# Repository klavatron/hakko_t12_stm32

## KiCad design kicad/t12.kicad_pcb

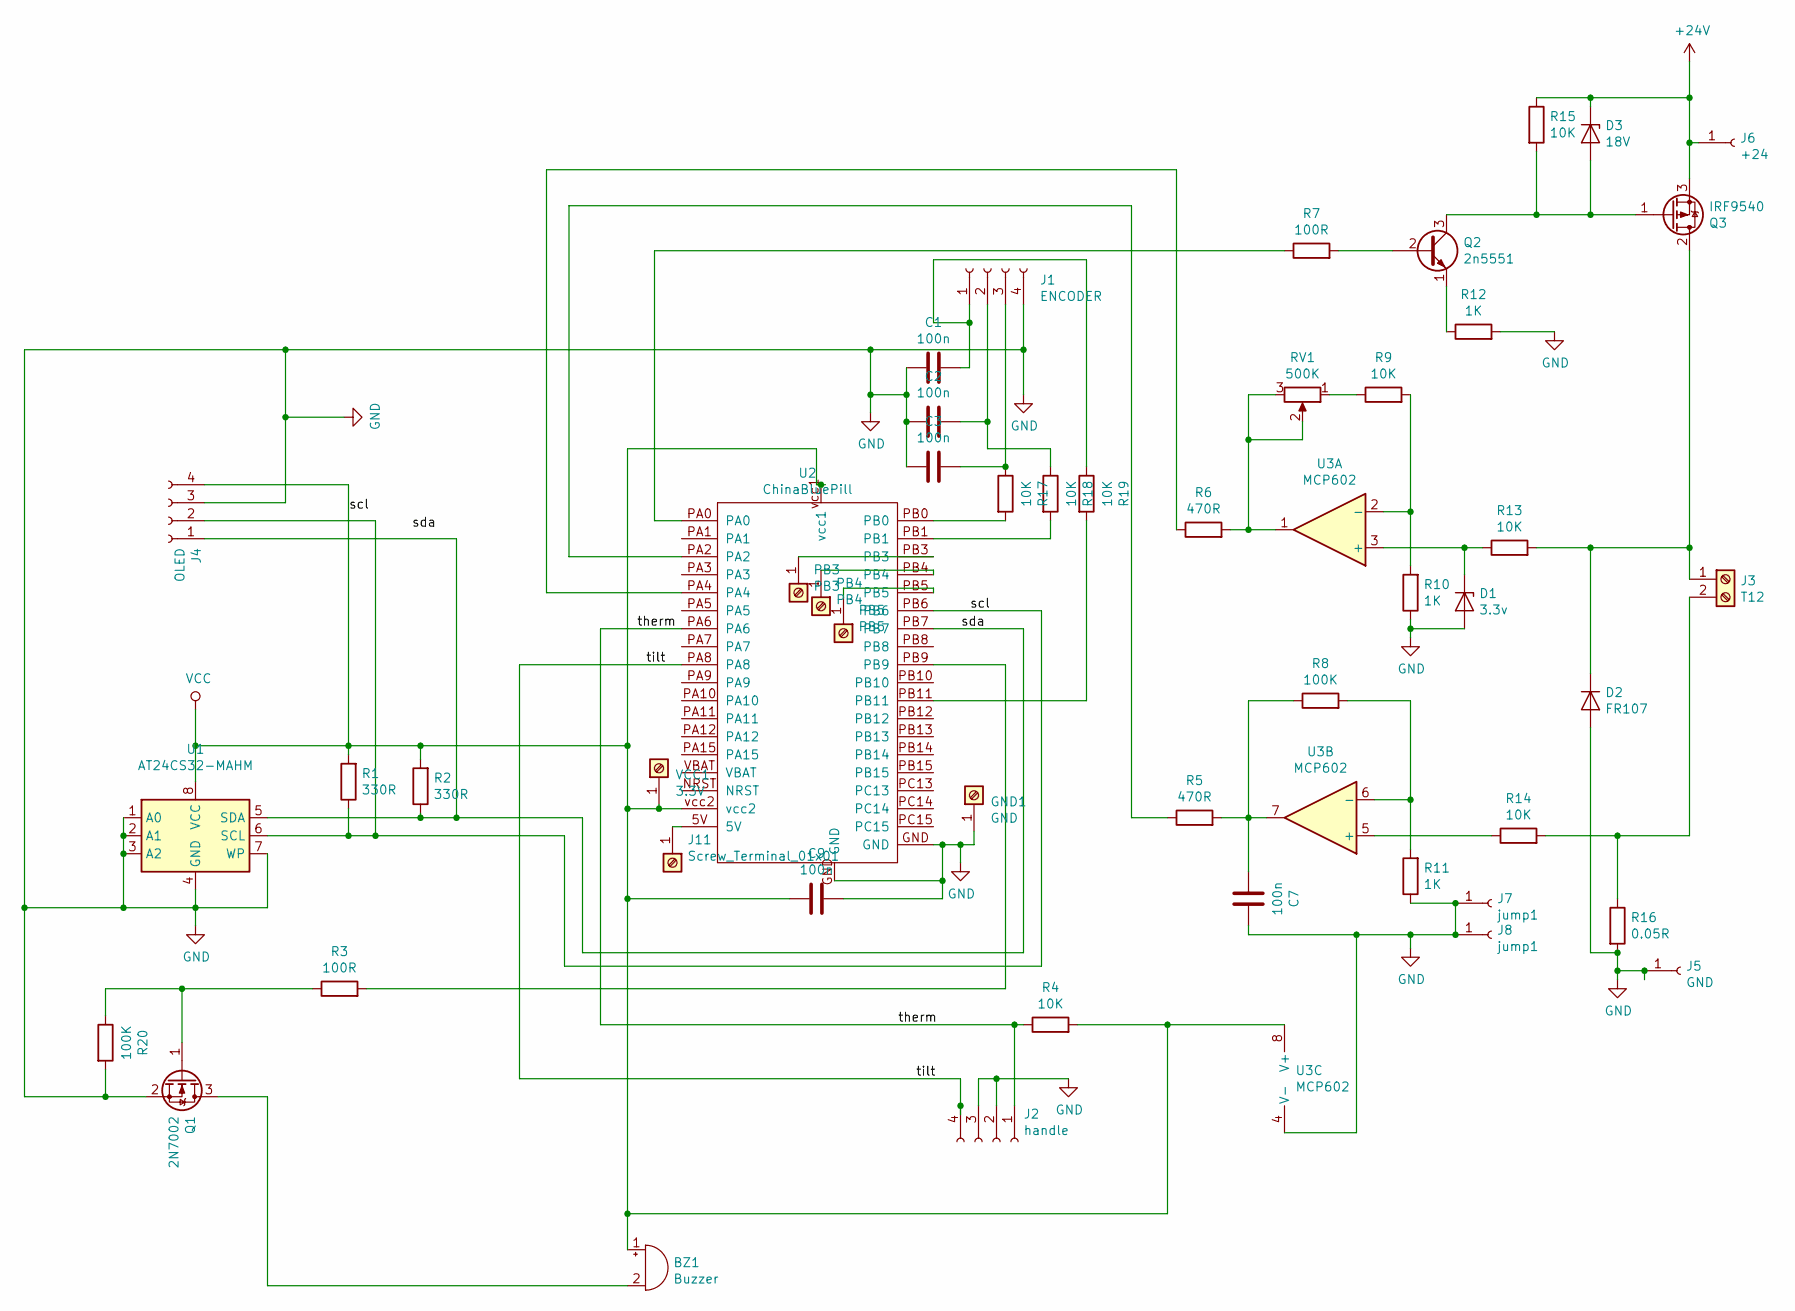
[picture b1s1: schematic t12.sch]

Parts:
BZ1: Buzzer; PinHeader_1x02_P2.54mm_Vertical
C1, C2, C3, C7, C9: 100n; C_1806_4516Metric
D1: 3.3v; D_DO-41_SOD81_P10.16mm_Horizontal
D2: FR107; D_DO-41_SOD81_P12.70mm_Horizontal
D3: 18V; D_DO-41_SOD81_P10.16mm_Horizontal
GND1: GND; PinHeader_1x01_P2.54mm_Vertical
J1: ENCODER; PinHeader_1x04_P2.54mm_Vertical
J2: handle; PinHeader_1x04_P2.54mm_Vertical
J3: T12; TerminalBlock_Altech_AK300-2_P5.00mm
J4: OLED; PinHeader_1x04_P2.54mm_Vertical
J5: GND; PinHeader_1x01_P2.54mm_Vertical
J6: +24; PinHeader_1x01_P2.54mm_Vertical
J7, J8: jump1; PinHeader_1x01_P2.54mm_Vertical
J11: Screw_Terminal_01x01; PinHeader_1x01_P2.54mm_Vertical
PB3: PB3; PinHeader_1x01_P2.54mm_Vertical
PB4: PB4; PinHeader_1x01_P2.54mm_Vertical
PB5: PB5; PinHeader_1x01_P2.54mm_Vertical
Q1: 2N7002; SOT-23
Q2: 2n5551; TO-92_Wide
Q3: IRF9540; TO-220-3_Vertical
R1: 330R; R_0805_2012Metric
R2: 330R; R_Axial_DIN0207_L6.3mm_D2.5mm_P10.16mm_Horizontal
R3: 100R; R_0805_2012Metric
R4, R9, R13, R14, R15, R17, R18, R19: 10K; R_0805_2012Metric
R5, R6: 470R; R_0805_2012Metric
R7: 100R; R_Axial_DIN0207_L6.3mm_D2.5mm_P10.16mm_Horizontal
R8, R20: 100K; R_0805_2012Metric
R10, R11, R12: 1K; R_0805_2012Metric
R16: 0.05R; R_Axial_DIN0614_L14.3mm_D5.7mm_P20.32mm_Horizontal
RV1: 500K; Potentiometer_Bourns_3296W_Vertical
U1: AT24CS32-MAHM; SOIC-8_3.9x4.9mm_P1.27mm
U2: ChinaBluePill
U3: MCP602; SOIC-8_3.9x4.9mm_P1.27mm
VCC1: 3.3V; PinHeader_1x01_P2.54mm_Vertical

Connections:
+24V: D3.1 (K), J6.1, Q3.3 (S), R15.1
/sda: J4.1, R2.1, U1.5 (SDA), U2.PB7
/therm: J2.1, R4.1, U2.PA6
/tilt: J2.4, U2.PA8
GND: C1.2, C2.2, C3.2, C7.1, C9.1, D1.2 (A), D2.2 (A), GND1.1, J1.4, J2.2, J2.3, J4.3, J5.1, J7.1, J8.1, Q1.2 (S), R10.1, R11.1, R12.2, R16.2, R20.2, U1.1 (A0), U1.2 (A1), U1.3 (A2), U1.4 (GND), U1.7 (WP), U2.GND, U3.4 (V-)
unnamed: BZ1.2 (+), Q1.3 (D)
unnamed: C1.1, J1.1, R19.1
unnamed: C2.1, J1.2, R18.1
unnamed: C3.1, J1.3, R17.1
unnamed: C7.2, R5.2, R8.1, U3.7
unnamed: D1.1 (K), R13.1, U3.3 (+)
unnamed: D2.1 (K), J3.1, Q3.2 (D), R13.2
unnamed: D3.2 (A), Q2.3 (C), Q3.1 (G), R15.2
unnamed: J3.2, R14.2, R16.1
unnamed: J11.1, U2.5V
unnamed: PB3.1, U2.PB3
unnamed: PB4.1, U2.PB4
unnamed: PB5.1, U2.PB5
unnamed: Q1.1 (G), R3.1, R20.1
unnamed: Q2.1 (E), R12.1
unnamed: Q2.2 (B), R7.2
unnamed: R3.2, U2.PB9
unnamed: R5.1, U2.PA2
unnamed: R6.1, U2.PA4
unnamed: R6.2, RV1.2, RV1.3, U3.1
unnamed: R7.1, U2.PA0
unnamed: R9.1, RV1.1
unnamed: R9.2, R10.2, U3.2 (-)
unnamed: R8.2, R11.2, U3.6 (-)
unnamed: R14.1, U3.5 (+)
unnamed: R17.2, U2.PB0
unnamed: R18.2, U2.PB1
unnamed: R19.2, U2.PB11
VCC: BZ1.1 (-), C9.2, J4.2, J4.4, R1.1, R1.2, R2.2, R4.2, U1.6 (SCL), U1.8 (VCC), U2.PB6, U2.vcc1, U2.vcc2, U3.8 (V+), VCC1.1

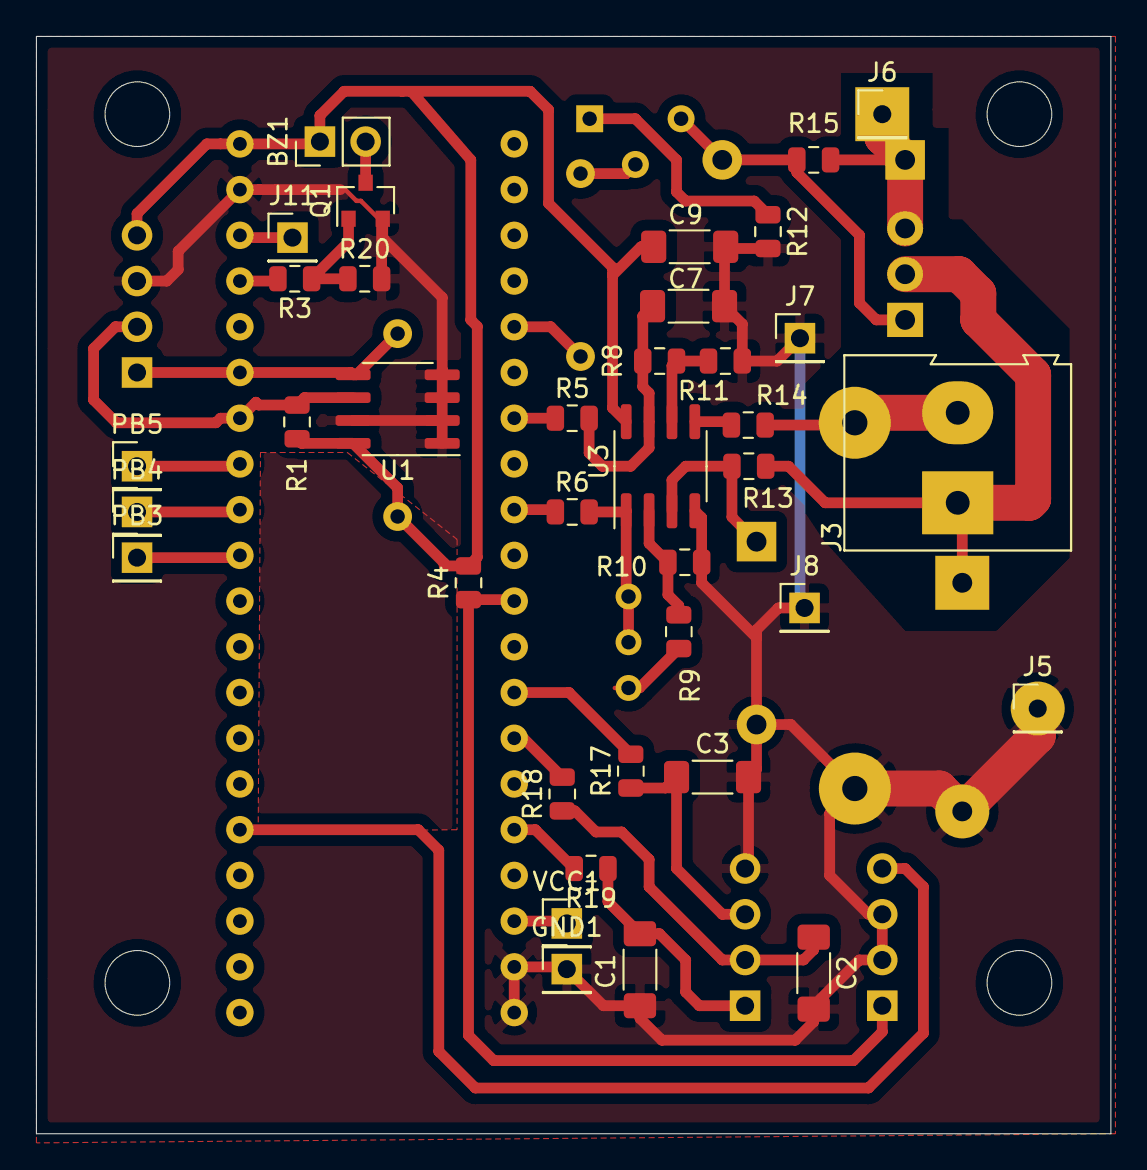
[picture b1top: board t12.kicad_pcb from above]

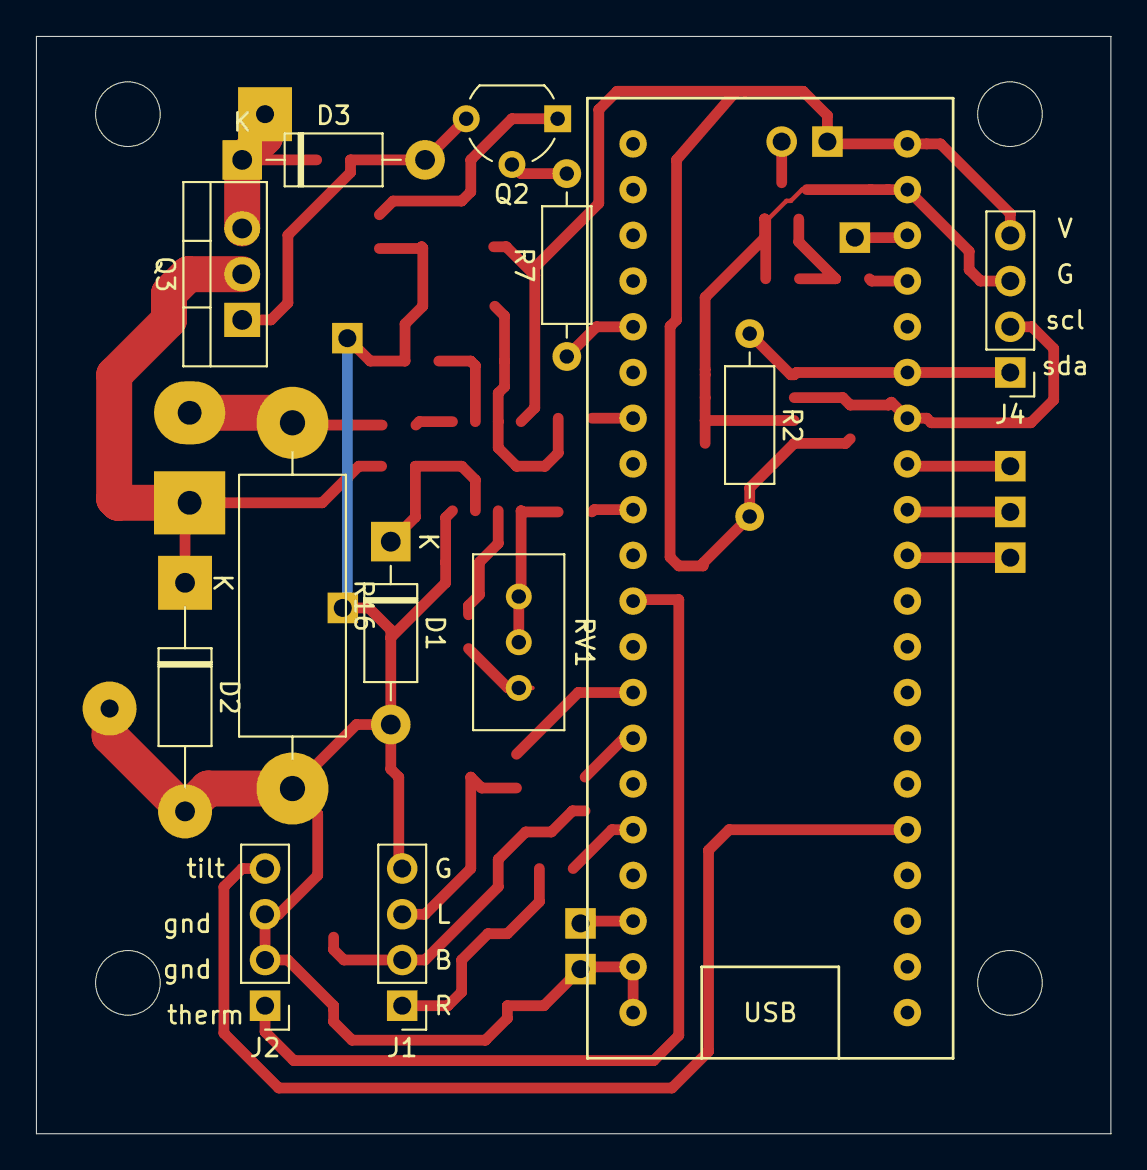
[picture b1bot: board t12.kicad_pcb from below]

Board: 2 copper layers, 59.7 x 61.0 mm, 50 parts (13 on the bottom side), 34 nets.

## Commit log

2020-01-19 kicad
2020-01-19 Removed OLED spi.
2020-01-19 Board preview
    kicad preview
2020-01-19 photos
    pcb photos
2020-01-21 cubemx project changes
